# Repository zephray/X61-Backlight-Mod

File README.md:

# X61-Backlight-Mod
LED Backlight Kit for ThinkPad X61. The driver board is based on Monty's TLD3 driver board design. It can output up to 600mA in buck mode.

## Useful Links

Monty's X61 Kit:
https://web.archive.org/web/20190318140731/https://people.xiph.org/~xiphmont/thinkpad/led-kit.shtml

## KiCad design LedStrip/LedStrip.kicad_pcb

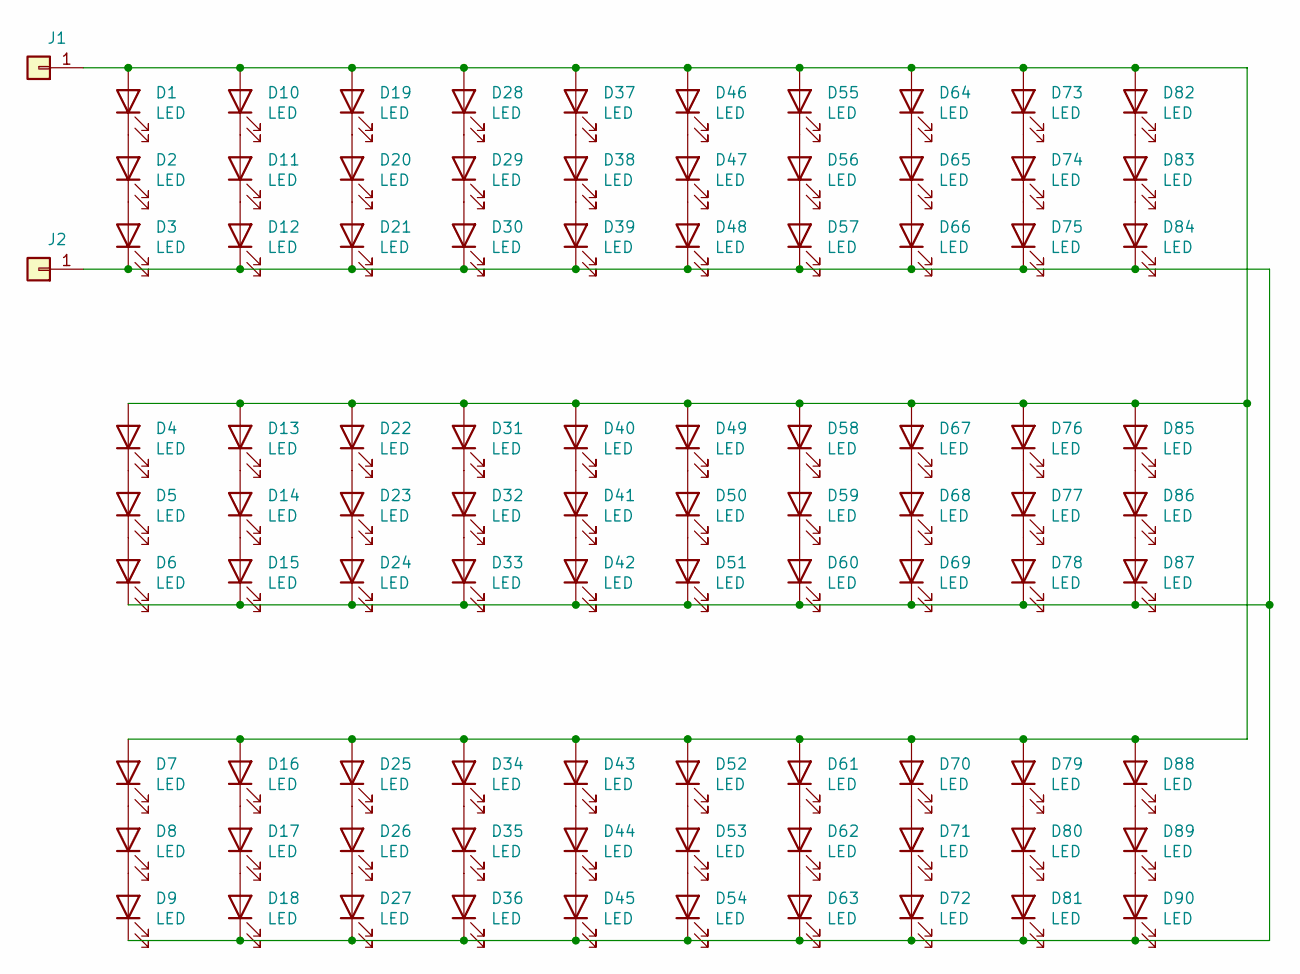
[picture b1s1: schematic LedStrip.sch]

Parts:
D1, D2, D3, D4, D5, D6, D7, D8, D9, D10, D11, D12, D13, D14, D15, D16, D17, D18, D19, D20, D21, D22, D23, D24, D25, D26, D27, D28, D29, D30, D31, D32, D33, D34, D35, D36, D37, D38, D39, D40, D41, D42, D43, D44, D45, D46, D47, D48, D49, D50, D51, D52, D53, D54, D55, D56, D57, D58, D59, D60, D61, D62, D63, D64, D65, D66, D67, D68, D69, D70, D71, D72, D73, D74, D75, D76, D77, D78, D79, D80, D81, D82, D83, D84, D85, D86, D87, D88, D89, D90: LED; LED_0805_2012Metric_Small
J1, J2: Conn_01x01; TestPoint_Pad_1.0x1.0mm

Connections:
unnamed: D1.1 (K), D2.2 (A)
unnamed: D1.2 (A), D4.2 (A), D7.2 (A), D10.2 (A), D13.2 (A), D16.2 (A), D19.2 (A), D22.2 (A), D25.2 (A), D28.2 (A), D31.2 (A), D34.2 (A), D37.2 (A), D40.2 (A), D43.2 (A), D46.2 (A), D49.2 (A), D52.2 (A), D55.2 (A), D58.2 (A), D61.2 (A), D64.2 (A), D67.2 (A), D70.2 (A), D73.2 (A), D76.2 (A), D79.2 (A), D82.2 (A), D85.2 (A), D88.2 (A), J1.1
unnamed: D2.1 (K), D3.2 (A)
unnamed: D4.1 (K), D5.2 (A)
unnamed: D5.1 (K), D6.2 (A)
unnamed: D7.1 (K), D8.2 (A)
unnamed: D8.1 (K), D9.2 (A)
unnamed: D10.1 (K), D11.2 (A)
unnamed: D11.1 (K), D12.2 (A)
unnamed: D3.1 (K), D6.1 (K), D9.1 (K), D12.1 (K), D15.1 (K), D18.1 (K), D21.1 (K), D24.1 (K), D27.1 (K), D30.1 (K), D33.1 (K), D36.1 (K), D39.1 (K), D42.1 (K), D45.1 (K), D48.1 (K), D51.1 (K), D54.1 (K), D57.1 (K), D60.1 (K), D63.1 (K), D66.1 (K), D69.1 (K), D72.1 (K), D75.1 (K), D78.1 (K), D81.1 (K), D84.1 (K), D87.1 (K), D90.1 (K), J2.1
unnamed: D13.1 (K), D14.2 (A)
unnamed: D14.1 (K), D15.2 (A)
unnamed: D16.1 (K), D17.2 (A)
unnamed: D17.1 (K), D18.2 (A)
unnamed: D19.1 (K), D20.2 (A)
unnamed: D20.1 (K), D21.2 (A)
unnamed: D22.1 (K), D23.2 (A)
unnamed: D23.1 (K), D24.2 (A)
unnamed: D25.1 (K), D26.2 (A)
unnamed: D26.1 (K), D27.2 (A)
unnamed: D28.1 (K), D29.2 (A)
unnamed: D29.1 (K), D30.2 (A)
unnamed: D31.1 (K), D32.2 (A)
unnamed: D32.1 (K), D33.2 (A)
unnamed: D34.1 (K), D35.2 (A)
unnamed: D35.1 (K), D36.2 (A)
unnamed: D37.1 (K), D38.2 (A)
unnamed: D38.1 (K), D39.2 (A)
unnamed: D40.1 (K), D41.2 (A)
unnamed: D41.1 (K), D42.2 (A)
unnamed: D43.1 (K), D44.2 (A)
unnamed: D44.1 (K), D45.2 (A)
unnamed: D46.1 (K), D47.2 (A)
unnamed: D47.1 (K), D48.2 (A)
unnamed: D49.1 (K), D50.2 (A)
unnamed: D50.1 (K), D51.2 (A)
unnamed: D52.1 (K), D53.2 (A)
unnamed: D53.1 (K), D54.2 (A)
unnamed: D55.1 (K), D56.2 (A)
unnamed: D56.1 (K), D57.2 (A)
unnamed: D58.1 (K), D59.2 (A)
unnamed: D59.1 (K), D60.2 (A)
unnamed: D61.1 (K), D62.2 (A)
unnamed: D62.1 (K), D63.2 (A)
unnamed: D64.1 (K), D65.2 (A)
unnamed: D65.1 (K), D66.2 (A)
unnamed: D67.1 (K), D68.2 (A)
unnamed: D68.1 (K), D69.2 (A)
unnamed: D70.1 (K), D71.2 (A)
unnamed: D71.1 (K), D72.2 (A)
unnamed: D73.1 (K), D74.2 (A)
unnamed: D74.1 (K), D75.2 (A)
unnamed: D76.1 (K), D77.2 (A)
unnamed: D77.1 (K), D78.2 (A)
unnamed: D79.1 (K), D80.2 (A)
unnamed: D80.1 (K), D81.2 (A)
unnamed: D82.1 (K), D83.2 (A)
unnamed: D83.1 (K), D84.2 (A)
unnamed: D85.1 (K), D86.2 (A)
unnamed: D86.1 (K), D87.2 (A)
unnamed: D88.1 (K), D89.2 (A)
unnamed: D89.1 (K), D90.2 (A)

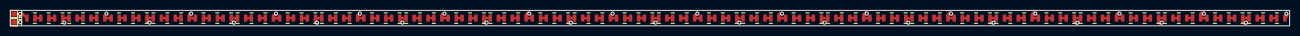
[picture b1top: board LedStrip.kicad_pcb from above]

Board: 2 copper layers, 249.0 x 3.0 mm, 92 parts (0 on the bottom side), 62 nets.

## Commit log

2020-08-18 pcb: initial schematic design for driver board
2020-08-19 pcb: r0p1
